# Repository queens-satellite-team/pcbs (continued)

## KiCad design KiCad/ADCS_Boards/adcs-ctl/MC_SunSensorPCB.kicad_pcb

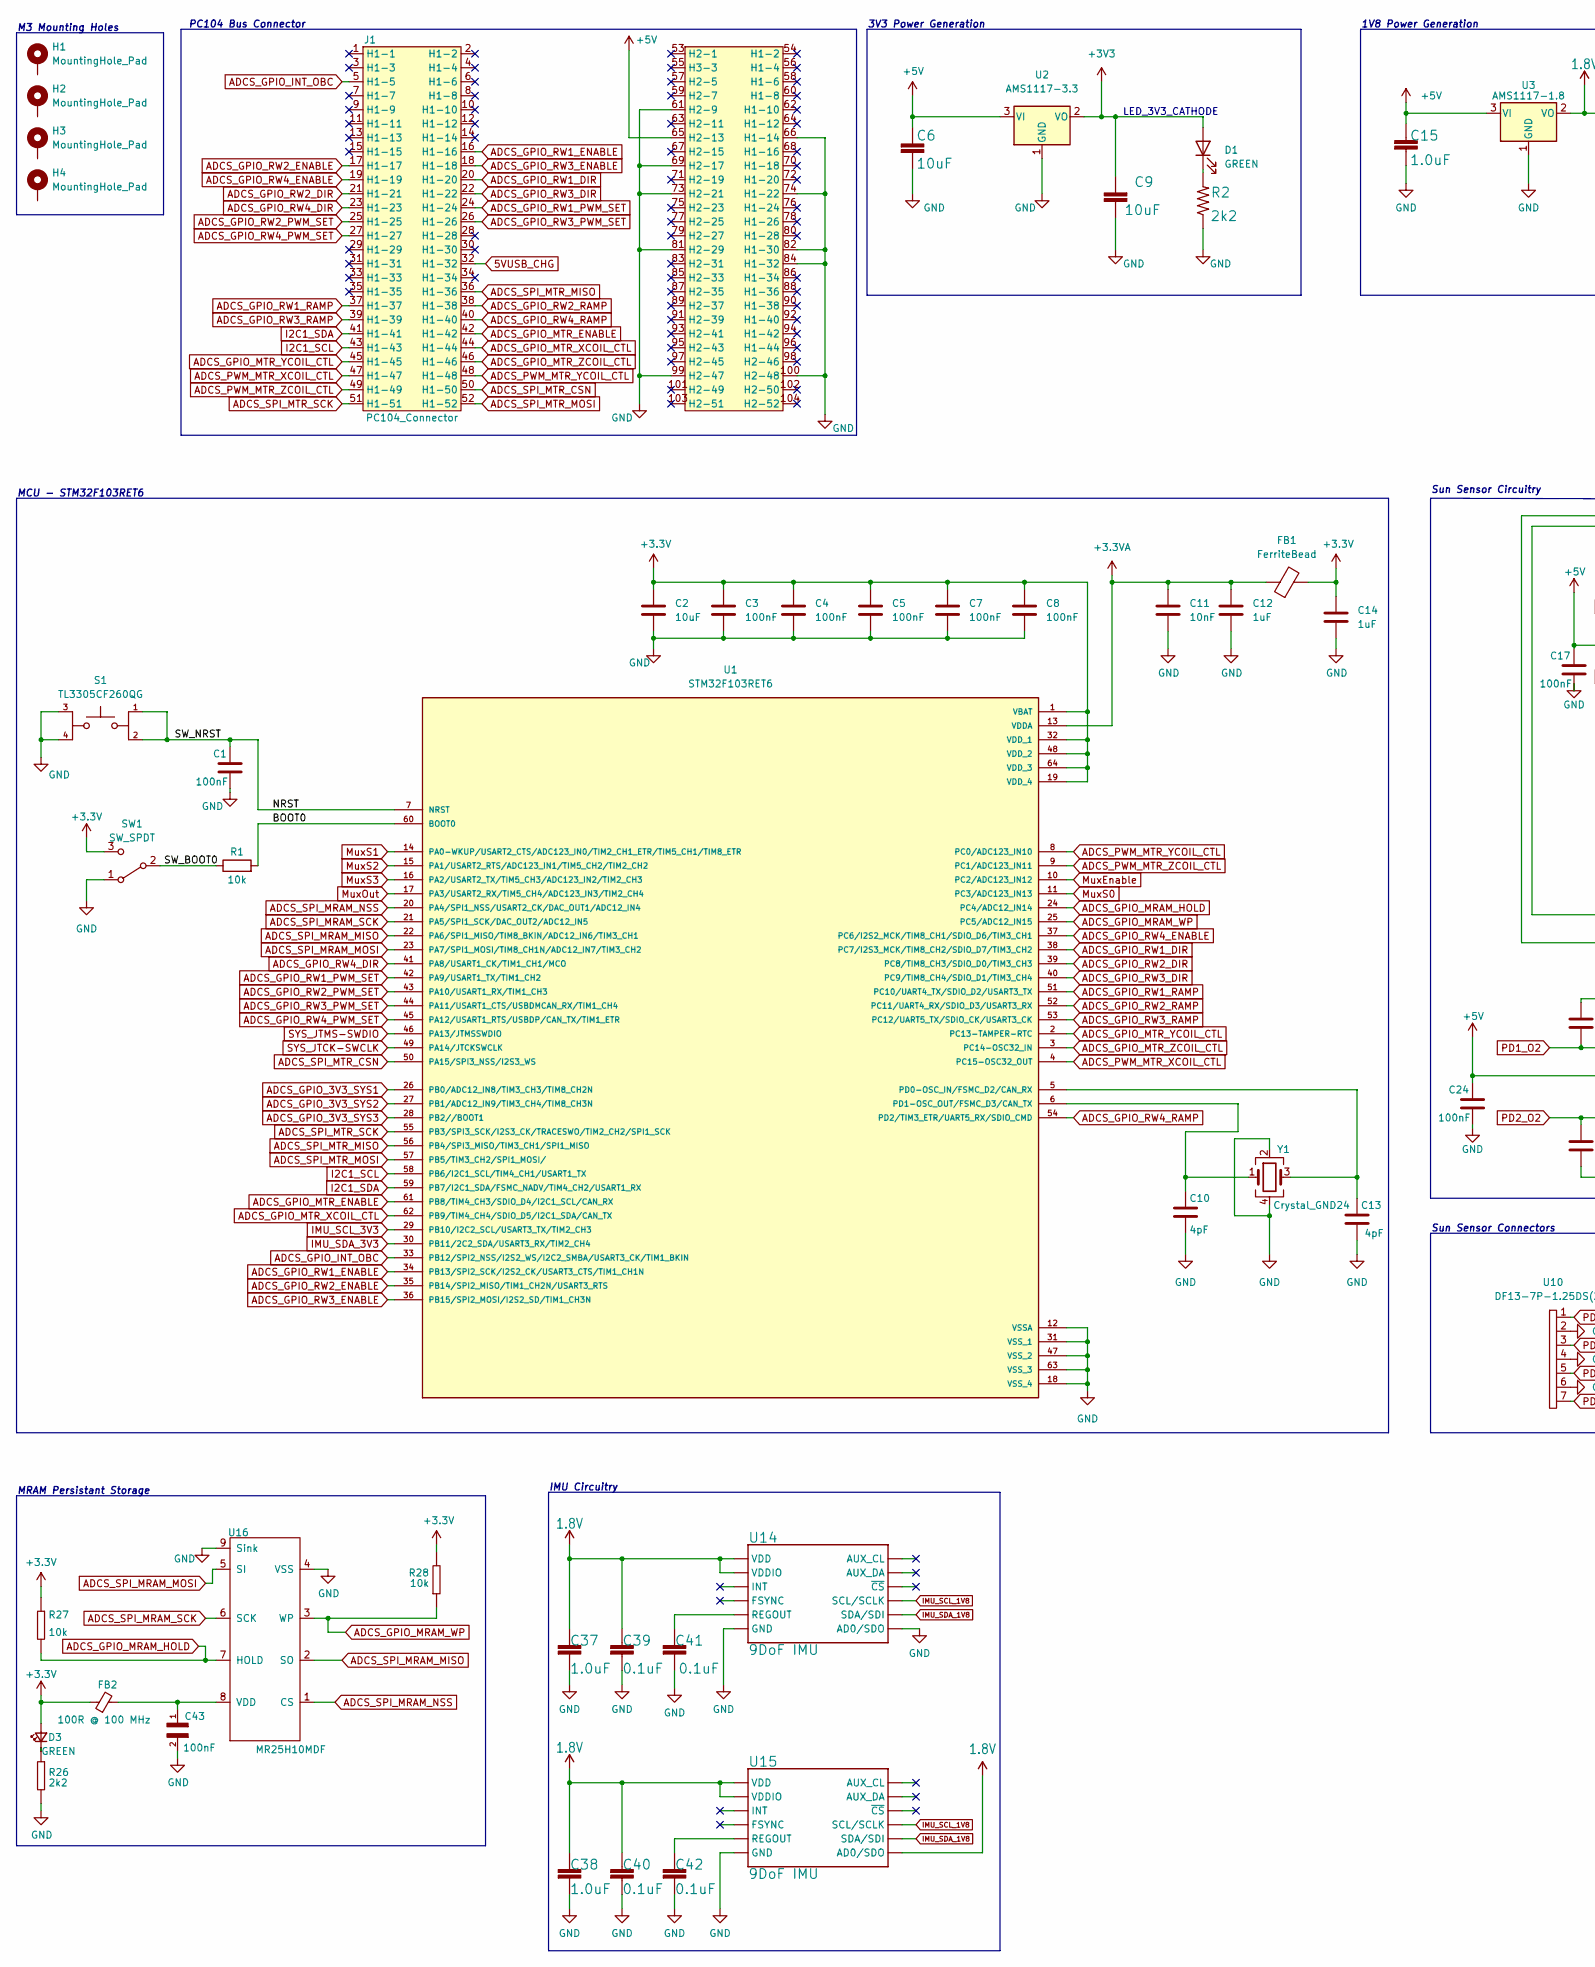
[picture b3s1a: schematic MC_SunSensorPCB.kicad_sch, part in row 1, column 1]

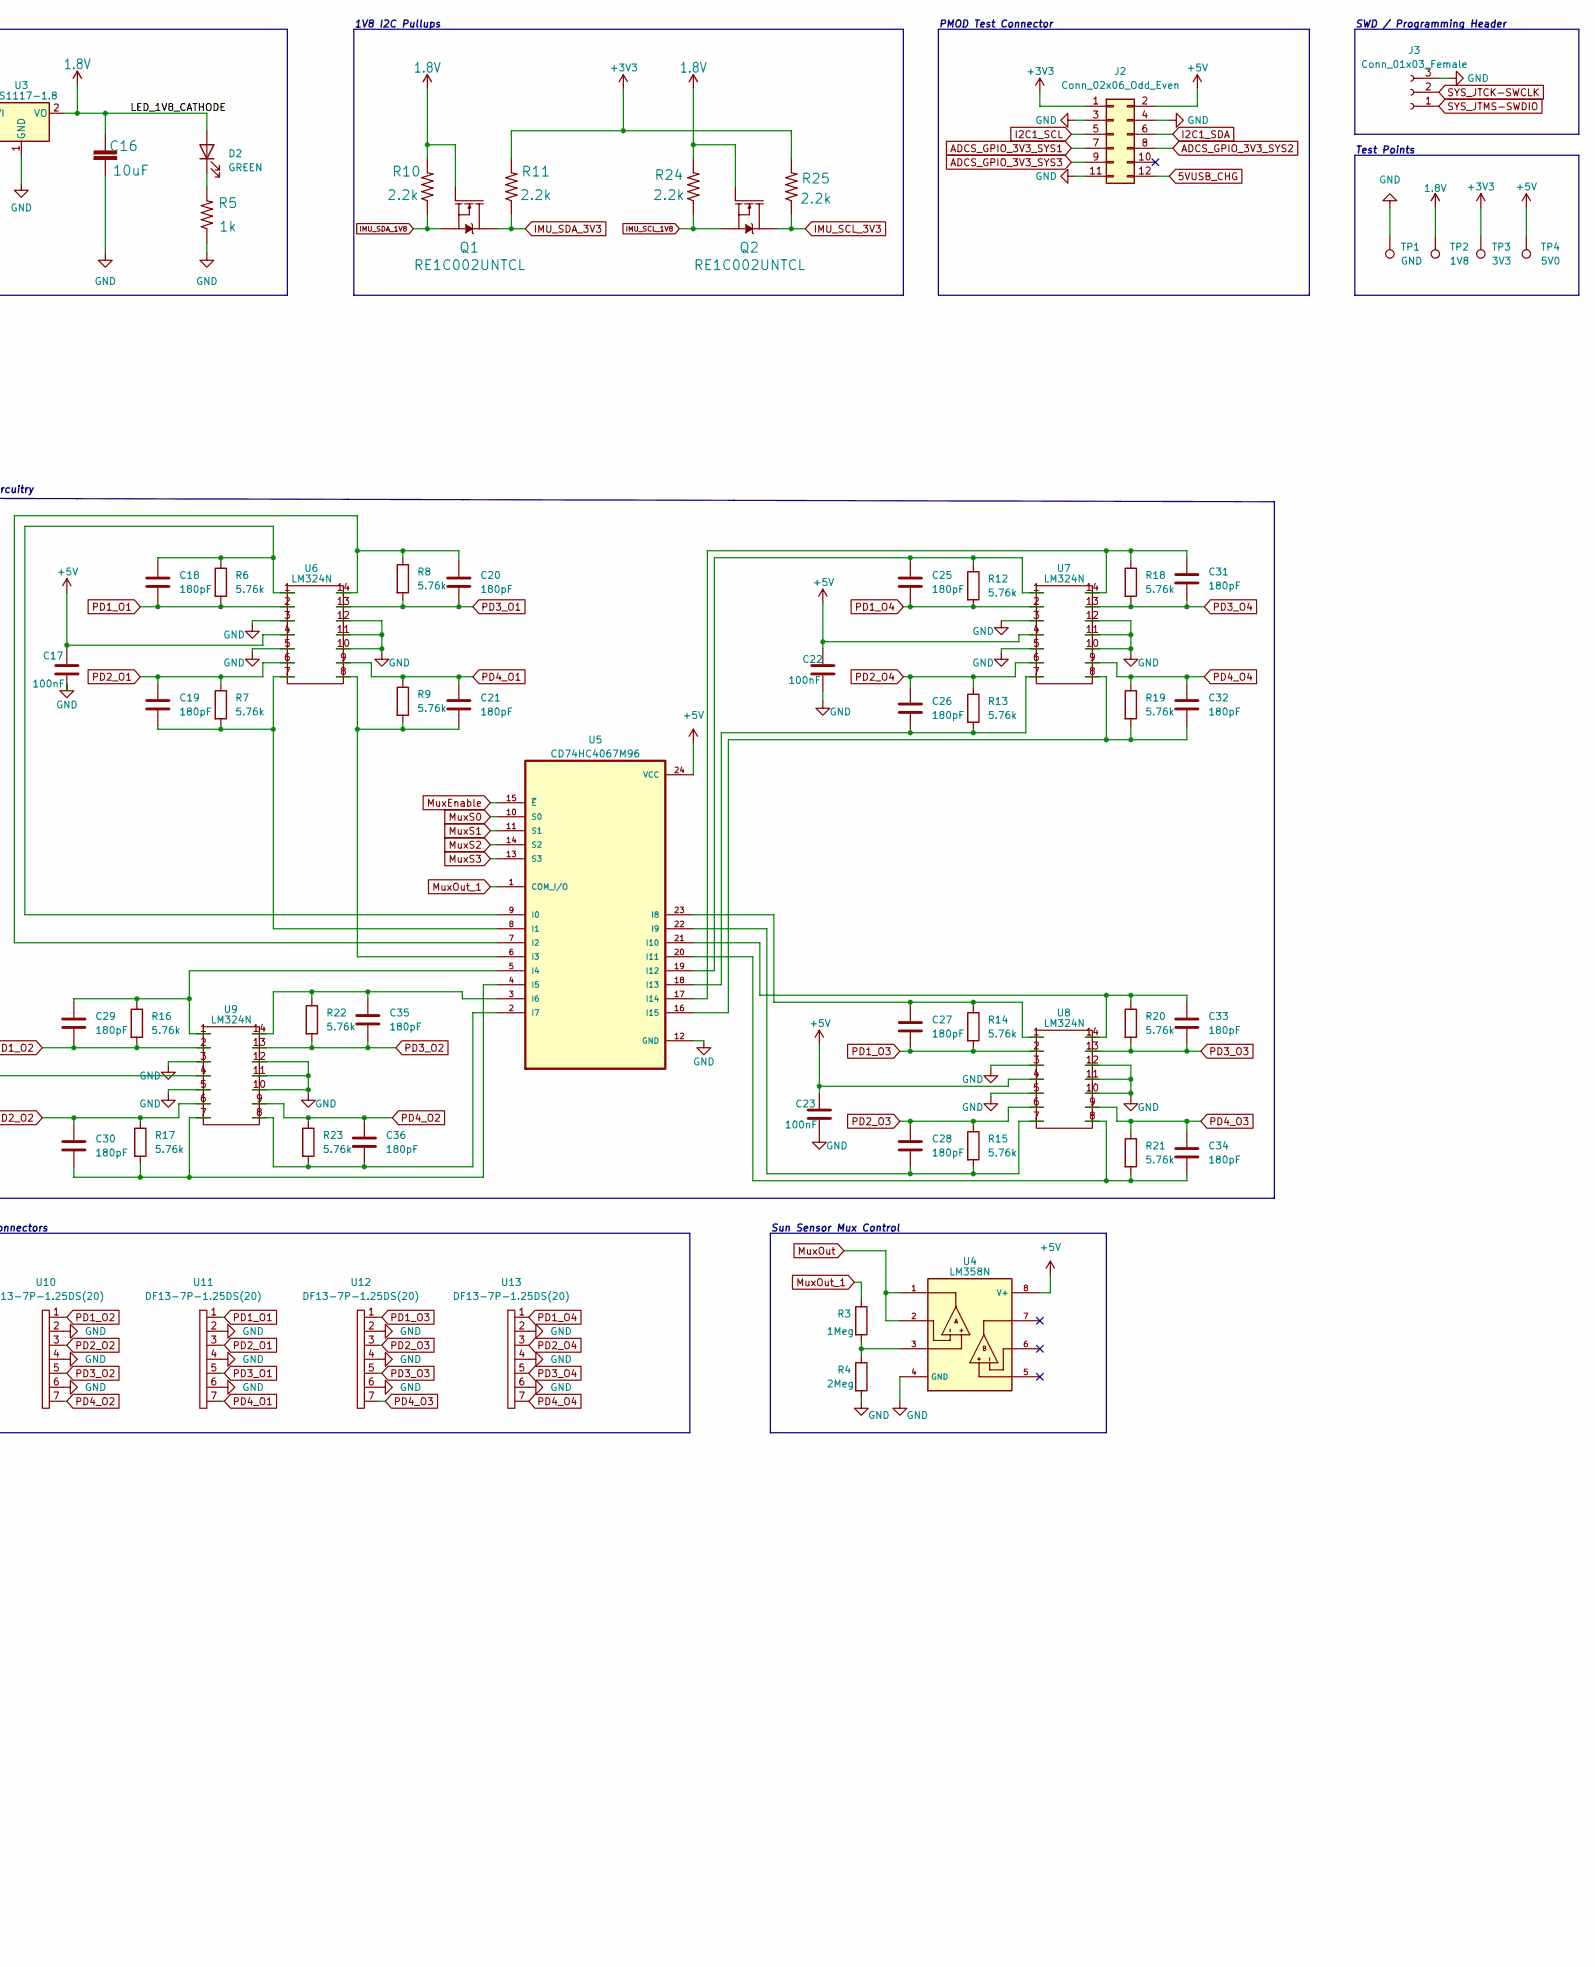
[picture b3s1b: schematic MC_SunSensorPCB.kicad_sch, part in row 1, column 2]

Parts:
C1, C17, C22, C23, C24, C43: 100nF; C_0603_1608Metric
C2, C6, C9, C16: 10uF; C_0603_1608Metric
C3, C4, C5, C7, C8: 100nF; C_0402_1005Metric
C10, C13: 4pF; C_0402_1005Metric
C11: 10nF; C_0402_1005Metric
C12, C14: 1uF; C_0603_1608Metric
C15, C37, C38: 1.0uF; C_0603_1608Metric
C18, C19, C20, C21, C25, C26, C27, C28, C29, C30, C31, C32, C33, C34, C35, C36: 180pF; C_0603_1608Metric
C39, C40, C41, C42: 0.1uF; C_0603_1608Metric
D1, D2, D3: GREEN; LED_0603_1608Metric
FB1: FerriteBead; L_0603_1608Metric
FB2: 100R @ 100 MHz; L_0603_1608Metric
H1, H2, H3, H4: MountingHole_Pad; MountingHole_3.2mm_M3_Pad_TopBottom
J1: PC104_Connector; pc104-connector
J2: Conn_02x06_Odd_Even; PinSocket_2x06_P2.54mm_Horizontal
J3: Conn_01x03_Female; PinHeader_1x03_P2.54mm_Vertical
Q1, Q2: RE1C002UNTCL
R1: 10k; R_0603_1608Metric
R2, R26: 2k2; R_0603_1608Metric
R3: 1Meg; R_0603_1608Metric
R4: 2Meg; R_0603_1608Metric
R5: 1k; R_0603_1608Metric
R6, R7, R8, R9, R12, R13, R14, R15, R16, R17, R18, R19, R20, R21, R22, R23: 5.76k; R_0603_1608Metric
R10, R11, R24, R25: 2.2k; R_0603_1608Metric
R27, R28: 10k; R_0402_1005Metric
S1: TL3305CF260QG; SW_TL3305CF260QG; PARTREV C
SW1: SW_SPDT; SW_SPDT_PCM12
TP1: GND; TestPoint_THTPad_2.0x2.0mm_Drill1.0mm
TP2: 1V8; TestPoint_THTPad_2.0x2.0mm_Drill1.0mm
TP3: 3V3; TestPoint_THTPad_2.0x2.0mm_Drill1.0mm
TP4: 5V0; TestPoint_THTPad_2.0x2.0mm_Drill1.0mm
U1: STM32F103RET6; QFP50P1200X1200X160-64N
U2: AMS1117-3.3; SOT-223-3_TabPin2
U3: AMS1117-1.8; SOT-223-3_TabPin2
U4: LM358N; DIP794W45P254L959H508Q8
U5: CD74HC4067M96; SOIC127P1030X265-24N
U6, U7, U8, U9: LM324N; Op-Amp
U10, U11, U12, U13: DF13-7P-1.25DS(20); Hirose_DF13-07P-1.25DS_1x07_P1.25mm_Horizontal
U14, U15: 9DoF IMU; QFN24-3X3
U16: MR25H10MDF; SON65P300X300X95-8N
Y1: Crystal_GND24; Crystal_SMD_3225-4Pin_3.2x2.5mm

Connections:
1.8V: C16.1, C37.1, C38.1, C39.1, C40.1, D2.2 (A), Q1.1 (G), Q2.1 (G), R10.2, R24.2, TP2.1, U3.2 (VO), U14.8 (VDDIO), U14.13 (VDD), U15.8 (VDDIO), U15.9 (AD0/SDO), U15.13 (VDD)
5VUSB_CHG: J1.32 (H1-32), J2.12
+3.3VA: C11.1, C12.1, FB1.1, U1.13 (VDDA)
+5V: C6.1, C15.1, C17.1, C22.1, C23.1, C24.1, J1.65 (H2-13), J2.2, TP4.1, U2.3 (VI), U3.3 (VI), U4.8 (V+), U5.24 (VCC), U6.4, U7.4, U8.4, U9.4
/BOOT0: R1.2, U1.60 (BOOT0)
/NRST: C1.1, S1.1, S1.2, U1.7 (NRST); also elsewhere on the board
/SW_BOOT0: R1.1, SW1.2 (B)
ADCS_GPIO_3V3_SYS1: J2.7, U1.26 (PB0/ADC12_IN8/TIM3_CH3/TIM8_CH2N)
ADCS_GPIO_3V3_SYS2: J2.8, U1.27 (PB1/ADC12_IN9/TIM3_CH4/TIM8_CH3N)
ADCS_GPIO_3V3_SYS3: J2.9, U1.28 (PB2//BOOT1)
ADCS_GPIO_INT_OBC: J1.5 (H1-5), U1.33 (PB12/SPI2_NSS/I2S2_WS/I2C2_SMBA/USART3_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)
ADCS_GPIO_MRAM_HOLD: R27.2, U1.24 (PC4/ADC12_IN14), U16.7 (HOLD)
ADCS_GPIO_MRAM_WP: R28.1, U1.25 (PC5/ADC12_IN15), U16.3 (WP)
ADCS_GPIO_MTR_ENABLE: J1.42 (H1-42), U1.61 (PB8/TIM4_CH3/SDIO_D4/I2C1_SCL/CAN_RX)
ADCS_GPIO_MTR_XCOIL_CTL: J1.44 (H1-44), U1.62 (PB9/TIM4_CH4/SDIO_D5/I2C1_SDA/CAN_TX)
ADCS_GPIO_MTR_YCOIL_CTL: J1.45 (H1-45), U1.2 (PC13-TAMPER-RTC)
ADCS_GPIO_MTR_ZCOIL_CTL: J1.46 (H1-46), U1.3 (PC14-OSC32_IN)
ADCS_GPIO_RW1_DIR: J1.20 (H1-20), U1.38 (PC7/I2S3_MCK/TIM8_CH2/SDIO_D7/TIM3_CH2)
ADCS_GPIO_RW1_ENABLE: J1.16 (H1-16), U1.34 (PB13/SPI2_SCK/I2S2_CK/USART3_CTS/TIM1_C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)
ADCS_GPIO_RW1_PWM_SET: J1.24 (H1-24), U1.42 (PA9/USART1_TX/TIM1_CH2)
ADCS_GPIO_RW1_RAMP: J1.37 (H1-37), U1.51 (PC10/UART4_TX/SDIO_D2/USART3_TX)
ADCS_GPIO_RW2_DIR: J1.21 (H1-21), U1.39 (PC8/TIM8_CH3/SDIO_D0/TIM3_CH3)
ADCS_GPIO_RW2_ENABLE: J1.17 (H1-17), U1.35 (PB14/SPI2_MISO/TIM1_CH2N/USART3_RTS)
ADCS_GPIO_RW2_PWM_SET: J1.25 (H1-25), U1.43 (PA10/USART1_RX/TIM1_CH3)
ADCS_GPIO_RW2_RAMP: J1.38 (H1-38), U1.52 (PC11/UART4_RX/SDIO_D3/USART3_RX)
ADCS_GPIO_RW3_DIR: J1.22 (H1-22), U1.40 (PC9/TIM8_CH4/SDIO_D1/TIM3_CH4)
ADCS_GPIO_RW3_ENABLE: J1.18 (H1-18), U1.36 (PB15/SPI2_MOSI/I2S2_SD/TIM1_CH3N)
ADCS_GPIO_RW3_PWM_SET: J1.26 (H1-26), U1.44 (PA11/USART1_CTS/USBDMCAN_RX/TIM1_CH4)
ADCS_GPIO_RW3_RAMP: J1.39 (H1-39), U1.53 (PC12/UART5_TX/SDIO_CK/USART3_CK)
ADCS_GPIO_RW4_DIR: J1.23 (H1-23), U1.41 (PA8/USART1_CK/TIM1_CH1/MCO)
ADCS_GPIO_RW4_ENABLE: J1.19 (H1-19), U1.37 (PC6/I2S2_MCK/TIM8_CH1/SDIO_D6/TIM3_CH1)
ADCS_GPIO_RW4_PWM_SET: J1.27 (H1-27), U1.45 (PA12/USART1_RTS/USBDP/CAN_TX/TIM1_ETR)
ADCS_GPIO_RW4_RAMP: J1.40 (H1-40), U1.54 (PD2/TIM3_ETR/UART5_RX/SDIO_CMD)
ADCS_PWM_MTR_XCOIL_CTL: J1.47 (H1-47), U1.4 (PC15-OSC32_OUT)
ADCS_PWM_MTR_YCOIL_CTL: J1.48 (H1-48), U1.8 (PC0/ADC123_IN10)
ADCS_PWM_MTR_ZCOIL_CTL: J1.49 (H1-49), U1.9 (PC1/ADC123_IN11)
ADCS_SPI_MRAM_MISO: U1.22 (PA6/SPI1_MISO/TIM8_BKIN/ADC12_IN6/TIM3_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), U16.2 (SO)
ADCS_SPI_MRAM_MOSI: U1.23 (PA7/SPI1_MOSI/TIM8_CH1N/ADC12_IN7/TIM3_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), U16.5 (SI)
ADCS_SPI_MRAM_NSS: U1.20 (PA4/SPI1_NSS/USART2_CK/DAC_OUT1/ADC12_I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), U16.1 (CS)
ADCS_SPI_MRAM_SCK: U1.21 (PA5/SPI1_SCK/DAC_OUT2/ADC12_IN5), U16.6 (SCK)
ADCS_SPI_MTR_CSN: J1.50 (H1-50), U1.50 (PA15/SPI3_NSS/I2S3_WS)
ADCS_SPI_MTR_MISO: J1.36 (H1-36), U1.56 (PB4/SPI3_MISO/TIM3_CH1/SPI1_MISO)
ADCS_SPI_MTR_MOSI: J1.52 (H1-52), U1.57 (PB5/TIM3_CH2/SPI1_MOSI/)
ADCS_SPI_MTR_SCK: J1.51 (H1-51), U1.55 (PB3/SPI3_SCK/I2S3_CK/TRACESWO/TIM2_CH2/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)
GND: C1.2, C2.2, C3.2, C4.2, C5.2, C6.2, C7.2, C8.2, C9.1, C10.2, C11.2, C12.2, C13.2, C14.2, C15.2, C16.2, C17.2, C22.2, C23.2, C24.2, C37.2, C38.2, C39.2, C40.2, C41.2, C42.2, C43.2, J1.61 (H2-9), J1.66 (H1-14), J1.69 (H2-17), J1.73 (H2-21), J1.74 (H1-22), J1.81 (H2-29), J1.82 (H1-30), J1.84 (H1-32), J1.99 (H2-47), J1.100 (H2-48), J2.3, J2.4, J2.11, J3.3, R2.1, R4.2, R5.1, R26.2, S1.3, S1.4, SW1.1 (A), TP1.1, U1.12 (VSSA), U1.18 (VSS_4), U1.31 (VSS_1), U1.47 (VSS_2), U1.63 (VSS_3), U2.1 (GND), U3.1 (GND), U4.4 (GND), U5.12 (GND), U6.3, U6.5, U6.10, U6.11, U6.12, U7.3, U7.5, U7.10, U7.11, U7.12, U8.3, U8.5, U8.10, U8.11, U8.12, U9.3, U9.5, U9.10, U9.11, U9.12, U10.2, U10.4, U10.6, U11.2, U11.4, U11.6, U12.2, U12.4, U12.6, U13.2, U13.4, U13.6, U14.9 (AD0/SDO), U14.18 (GND), U14.20 (GND), U15.18 (GND), U15.20 (GND), U16.4 (VSS), U16.9 (Sink), Y1.2, Y1.4; also elsewhere on the board
I2C1_SCL: J1.43 (H1-43), J2.5, U1.58 (PB6/I2C1_SCL/TIM4_CH1/USART1_TX)
I2C1_SDA: J1.41 (H1-41), J2.6, U1.59 (PB7/I2C1_SDA/FSMC_NADV/TIM4_CH2/USART1_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)
IMU_SCL_1V8: Q2.2 (S), R24.1, U14.23 (SCL/SCLK), U15.23 (SCL/SCLK)
IMU_SCL_3V3: Q2.3 (D), R25.1, U1.29 (PB10/I2C2_SCL/USART3_TX/TIM2_CH3)
IMU_SDA_1V8: Q1.2 (S), R10.1, U14.24 (SDA/SDI), U15.24 (SDA/SDI)
IMU_SDA_3V3: Q1.3 (D), R11.1, U1.30 (PB11/2C2_SDA/USART3_RX/TIM2_CH4)
MuxEnable: U1.10 (PC2/ADC123_IN12), U5.15 (~E)
MuxOut: U1.17 (PA3/USART2_RX/TIM5_CH4/ADC123_IN3/TIM2_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), U4.1, U4.2
MuxOut_1: R3.1, U5.1 (COM_I/O)
MuxS0: U1.11 (PC3/ADC123_IN13), U5.10 (S0)
MuxS1: U1.14 (PA0-WKUP/USART2_CTS/ADC123_IN0/TIM2_CH1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), U5.11 (S1)
MuxS2: U1.15 (PA1/USART2_RTS/ADC123_IN1/TIM5_CH2/TIM2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), U5.14 (S2)
MuxS3: U1.16 (PA2/USART2_TX/TIM5_CH3/ADC123_IN2/TIM2_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), U5.13 (S3)
unnamed: C10.1, U1.6 (PD1-OSC_OUT/FSMC_D3/CAN_TX), Y1.1
unnamed: C13.1, U1.5 (PD0-OSC_IN/FSMC_D2/CAN_RX), Y1.3
unnamed: C18.1, R6.1, U5.9 (I0), U6.1
unnamed: C19.1, R7.2, U5.8 (I1), U6.7
unnamed: C20.1, R8.1, U5.7 (I2), U6.14
unnamed: C21.2, R9.2, U5.6 (I3), U6.8
unnamed: C25.1, R12.1, U5.19 (I12), U7.1
unnamed: C26.1, R13.2, U5.18 (I13), U7.7
unnamed: C27.1, R14.1, U5.23 (I8), U8.1
unnamed: C28.1, R15.2, U5.22 (I9), U8.7
unnamed: C29.1, R16.1, U5.5 (I4), U9.1
unnamed: C30.1, R17.2, U5.4 (I5), U9.7
unnamed: C31.1, R18.1, U5.17 (I14), U7.14
unnamed: C32.2, R19.2, U5.16 (I15), U7.8
unnamed: C33.1, R20.1, U5.21 (I10), U8.14
unnamed: C34.2, R21.2, U5.20 (I11), U8.8
unnamed: C35.1, R22.1, U5.3 (I6), U9.14
unnamed: C36.2, R23.2, U5.2 (I7), U9.8
unnamed: C41.1, U14.10 (REGOUT)
unnamed: C42.1, U15.10 (REGOUT)
unnamed: C43.1, FB2.2, U16.8 (VDD)
unnamed: D1.1 (K), R2.2
unnamed: D2.1 (K), R5.2
unnamed: D3.1 (K), R26.1
unnamed: R3.2, R4.1, U4.3
PD1_O1: C18.2, R6.2, U6.2, U11.1
PD1_O2: C29.2, R16.2, U9.2, U10.1
PD1_O3: C27.2, R14.2, U8.2, U12.1
PD1_O4: C25.2, R12.2, U7.2, U13.1
PD2_O1: C19.2, R7.1, U6.6, U11.3
PD2_O2: C30.2, R17.1, U9.6, U10.3
PD2_O3: C28.2, R15.1, U8.6, U12.3
PD2_O4: C26.2, R13.1, U7.6, U13.3
PD3_O1: C20.2, R8.2, U6.13, U11.5
PD3_O2: C35.2, R22.2, U9.13, U10.5
PD3_O3: C33.2, R20.2, U8.13, U12.5
PD3_O4: C31.2, R18.2, U7.13, U13.5
PD4_O1: C21.1, R9.1, U6.9, U11.7
PD4_O2: C36.1, R23.1, U9.9, U10.7
PD4_O3: C34.1, R21.1, U8.9, U12.7
PD4_O4: C32.1, R19.1, U7.9, U13.7
SYS_JTCK-SWCLK: J3.2, U1.49 (PA14/JTCKSWCLK)
SYS_JTMS-SWDIO: J3.1, U1.46 (PA13/JTMSSWDIO)

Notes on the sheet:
PMOD Test Connector
Test Points
IMU Circuitry
1V8 I2C Pullups
Sun Sensor Mux Control
3V3 Power Generation
Sun Sensor Connectors
Sun Sensor Circuitry
MRAM Persistant Storage
PC104 Bus Connector
LED_3V3_CATHODE
SWD / Programming Header
1V8 Power Generation
M3 Mounting Holes
MCU - STM32F103RET6

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
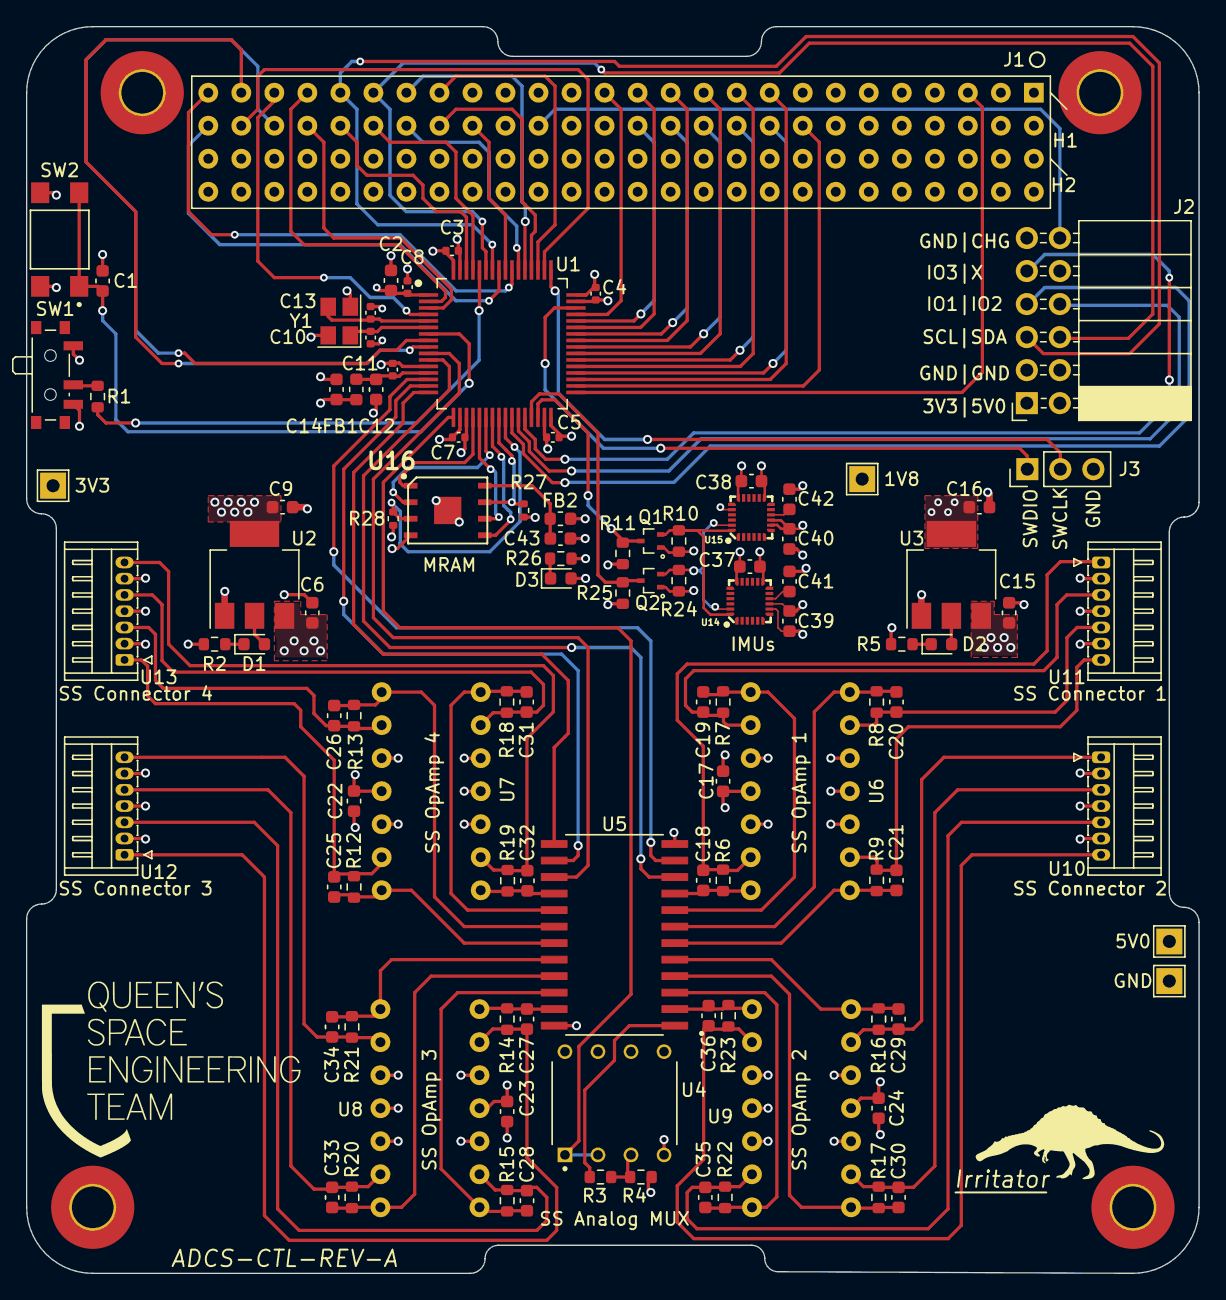
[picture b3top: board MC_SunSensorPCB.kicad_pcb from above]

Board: 4 copper layers, 90.2 x 95.9 mm, 108 parts (0 on the bottom side), 102 nets.

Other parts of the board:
SW2: TL3305CF260QG; SW_TL3305CF260QG

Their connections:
/NRST: SW2.1, SW2.2; also elsewhere on the board
GND: SW2.3, SW2.4; also elsewhere on the board

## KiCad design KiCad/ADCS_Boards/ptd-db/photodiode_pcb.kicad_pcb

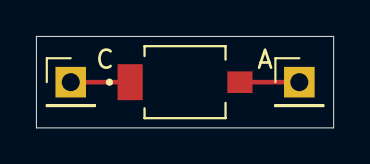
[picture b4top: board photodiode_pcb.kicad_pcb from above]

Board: 2 copper layers, 16.5 x 5.1 mm, 3 parts (0 on the bottom side), 2 nets.

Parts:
A: Conn_01x01; PinHeader_1x01_P2.54mm_Vertical
C: Conn_01x01; PinHeader_1x01_P2.54mm_Vertical
D1: SFH_2430-Z; DIO_SFH_2430-Z

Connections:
unnamed: A.1, D1.A
unnamed: C.1, D1.C
